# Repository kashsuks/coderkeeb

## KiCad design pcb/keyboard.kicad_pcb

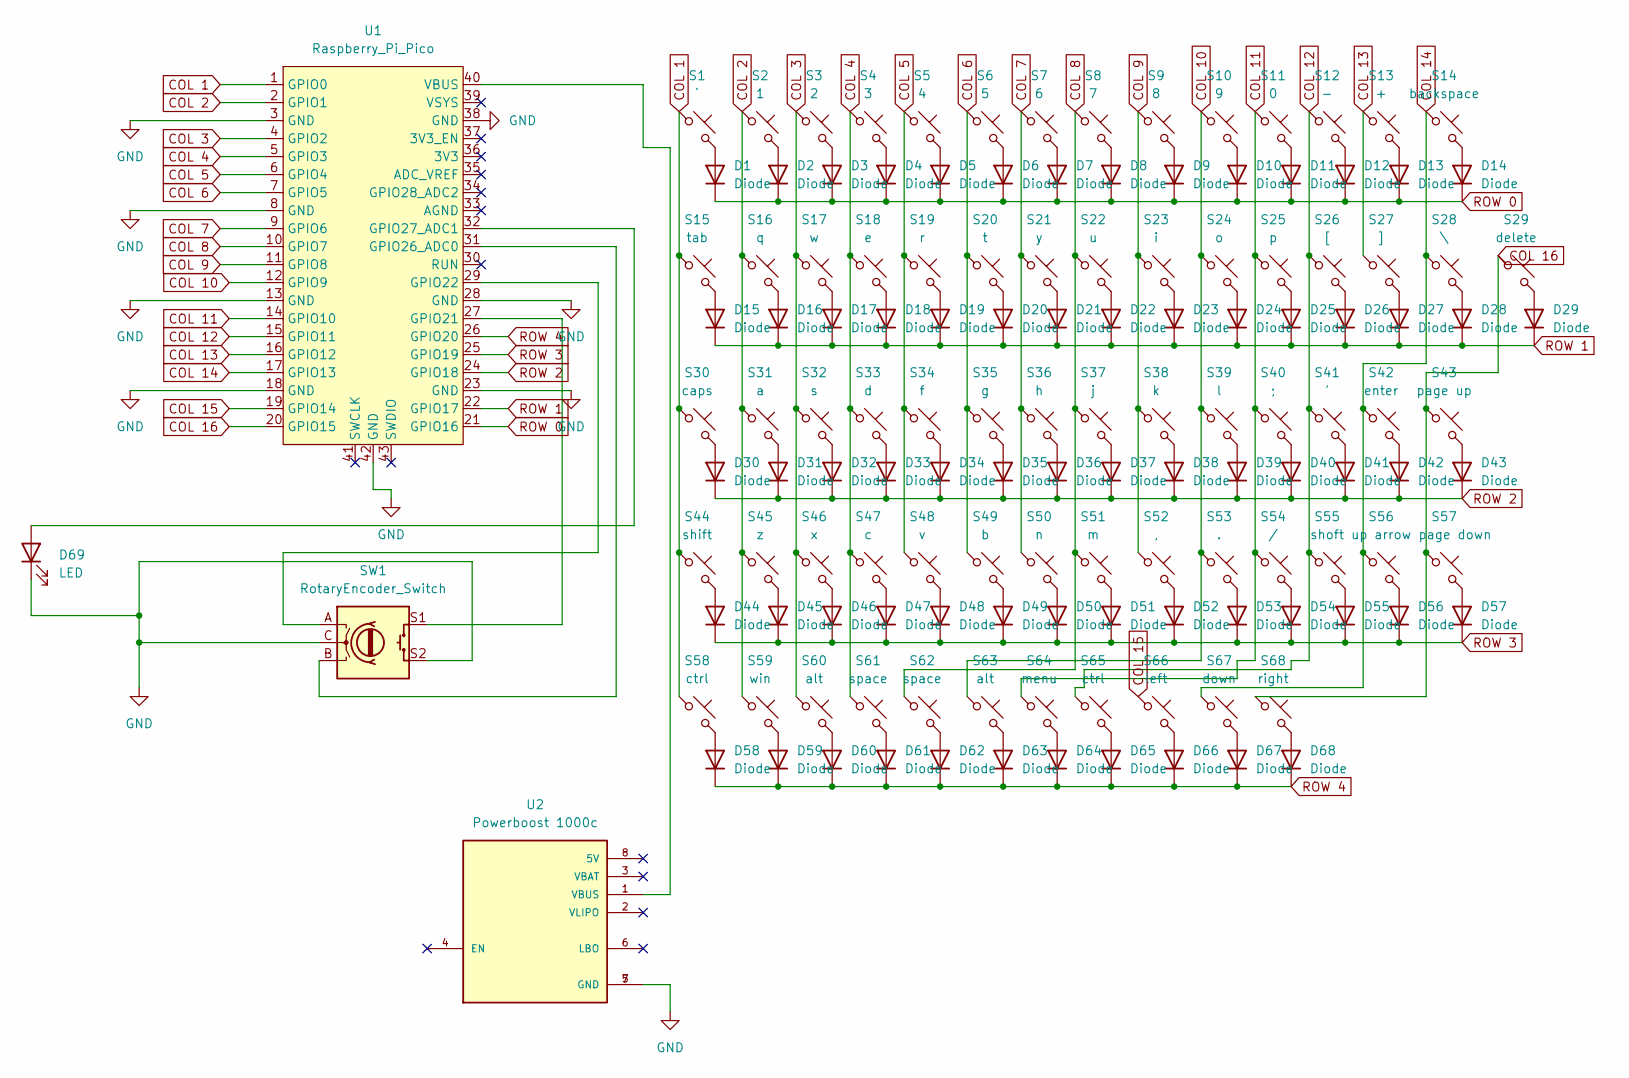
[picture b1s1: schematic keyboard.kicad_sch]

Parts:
D1, D2, D3, D4, D5, D6, D7, D8, D9, D10, D11, D12, D13, D14, D15, D16, D17, D18, D19, D20, D21, D22, D23, D24, D25, D26, D27, D28, D29, D30, D31, D32, D33, D34, D35, D36, D37, D38, D39, D40, D41, D42, D43, D44, D45, D46, D47, D48, D49, D50, D51, D52, D53, D54, D55, D56, D57, D58, D59, D60, D61, D62, D63, D64, D65, D66, D67, D68: Diode; Diode_DO-35
D69: LED; LED_D5.0mm
S1: `; Choc_V1
S2: 1; Choc_V1
S3: 2; Choc_V1
S4: 3; Choc_V1
S5: 4; Choc_V1
S6: 5; Choc_V1
S7: 6; Choc_V1
S8: 7; Choc_V1
S9: 8; Choc_V1
S10: 9; Choc_V1
S11: 0; Choc_V1
S12: -; Choc_V1
S13: +; Choc_V1
S14: backspace; Choc_V1
S15: tab; Choc_V1
S16: q; Choc_V1
S17: w; Choc_V1
S18: e; Choc_V1
S19: r; Choc_V1
S20: t; Choc_V1
S21: y; Choc_V1
S22: u; Choc_V1
S23: i; Choc_V1
S24: o; Choc_V1
S25: p; Choc_V1
S26: [; Choc_V1
S27: ]; Choc_V1
S28: \; Choc_V1
S29: delete; Choc_V1
S30: caps; Choc_V1
S31: a; Choc_V1
S32: s; Choc_V1
S33: d; Choc_V1
S34: f; Choc_V1
S35: g; Choc_V1
S36: h; Choc_V1
S37: j; Choc_V1
S38: k; Choc_V1
S39: l; Choc_V1
S40: ;; Choc_V1
S41: '; Choc_V1
S42: enter; Choc_V1
S43: page up; Choc_V1
S44: shift; Choc_V1
S45: z; Choc_V1
S46: x; Choc_V1
S47: c; Choc_V1
S48: v; Choc_V1
S49: b; Choc_V1
S50: n; Choc_V1
S51: m; Choc_V1
S52: ,; Choc_V1
S53: .; Choc_V1
S54: /; Choc_V1
S55: shoft; Choc_V1
S56: up arrow; Choc_V1
S57: page down; Choc_V1
S58, S65: ctrl; Choc_V1
S59: win; Choc_V1
S60, S63: alt; Choc_V1
S61, S62: space; Choc_V1
S64: menu; Choc_V1
S66: left; Choc_V1
S67: down; Choc_V1
S68: right; Choc_V1
SW1: RotaryEncoder_Switch; Encoder_EC11_MX
U1: Raspberry_Pi_Pico
U2: Powerboost 1000c; MODULE_2465; PARTREV B

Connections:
COL 1: S1.1, S15.1, S30.1, S44.1, S58.1, U1.1 (GPIO0)
COL 2: S2.1, S16.1, S31.1, S45.1, S59.1, U1.2 (GPIO1)
COL 3: S3.1, S17.1, S32.1, S46.1, S60.1, U1.4 (GPIO2)
COL 4: S4.1, S18.1, S33.1, S47.1, S61.1, U1.5 (GPIO3)
COL 5: S5.1, S19.1, S34.1, S48.1, U1.6 (GPIO4)
COL 6: S6.1, S20.1, S35.1, S49.1, U1.7 (GPIO5)
COL 7: S7.1, S21.1, S36.1, S50.1, U1.9 (GPIO6)
COL 8: S8.1, S22.1, S37.1, S51.1, S62.1, U1.10 (GPIO7)
COL 9: S9.1, S23.1, S38.1, S52.1, U1.11 (GPIO8)
COL 10: S10.1, S24.1, S39.1, S53.1, S63.1, U1.12 (GPIO9)
COL 11: S11.1, S25.1, S40.1, S54.1, S64.1, U1.14 (GPIO10)
COL 12: S12.1, S26.1, S41.1, S55.1, S65.1, U1.15 (GPIO11)
COL 13: S13.1, S27.1, U1.16 (GPIO12)
COL 14: S14.1, S28.1, S42.1, S56.1, S67.1, U1.17 (GPIO13)
COL 15: S66.1, U1.19 (GPIO14)
COL 16: S29.1, S43.1, S57.1, S68.1, U1.20 (GPIO15)
GND: D69.1 (K), SW1.C, SW1.S2, U1.3 (GND), U1.8 (GND), U1.13 (GND), U1.18 (GND), U1.23 (GND), U1.28 (GND), U1.38 (GND), U1.42 (GND), U2.5 (GND), U2.7 (GND)
unnamed: D1.2 (A), S1.2
unnamed: D2.2 (A), S2.2
unnamed: D3.2 (A), S3.2
unnamed: D4.2 (A), S4.2
unnamed: D5.2 (A), S5.2
unnamed: D6.2 (A), S6.2
unnamed: D7.2 (A), S7.2
unnamed: D8.2 (A), S8.2
unnamed: D9.2 (A), S9.2
unnamed: D10.2 (A), S10.2
unnamed: D11.2 (A), S11.2
unnamed: D12.2 (A), S12.2
unnamed: D13.2 (A), S13.2
unnamed: D14.2 (A), S14.2
unnamed: D15.2 (A), S15.2
unnamed: D16.2 (A), S16.2
unnamed: D17.2 (A), S17.2
unnamed: D18.2 (A), S18.2
unnamed: D19.2 (A), S19.2
unnamed: D20.2 (A), S20.2
unnamed: D21.2 (A), S21.2
unnamed: D22.2 (A), S22.2
unnamed: D23.2 (A), S23.2
unnamed: D24.2 (A), S24.2
unnamed: D25.2 (A), S25.2
unnamed: D26.2 (A), S26.2
unnamed: D27.2 (A), S27.2
unnamed: D28.2 (A), S28.2
unnamed: D29.2 (A), S29.2
unnamed: D30.2 (A), S30.2
unnamed: D31.2 (A), S31.2
unnamed: D32.2 (A), S32.2
unnamed: D33.2 (A), S33.2
unnamed: D34.2 (A), S34.2
unnamed: D35.2 (A), S35.2
unnamed: D36.2 (A), S36.2
unnamed: D37.2 (A), S37.2
unnamed: D38.2 (A), S38.2
unnamed: D39.2 (A), S39.2
unnamed: D40.2 (A), S40.2
unnamed: D41.2 (A), S41.2
unnamed: D42.2 (A), S42.2
unnamed: D43.2 (A), S43.2
unnamed: D44.2 (A), S44.2
unnamed: D45.2 (A), S45.2
unnamed: D46.2 (A), S46.2
unnamed: D47.2 (A), S47.2
unnamed: D48.2 (A), S48.2
unnamed: D49.2 (A), S49.2
unnamed: D50.2 (A), S50.2
unnamed: D51.2 (A), S51.2
unnamed: D52.2 (A), S52.2
unnamed: D53.2 (A), S53.2
unnamed: D54.2 (A), S54.2
unnamed: D55.2 (A), S55.2
unnamed: D56.2 (A), S56.2
unnamed: D57.2 (A), S57.2
unnamed: D58.2 (A), S58.2
unnamed: D59.2 (A), S59.2
unnamed: D60.2 (A), S60.2
unnamed: D61.2 (A), S61.2
unnamed: D62.2 (A), S62.2
unnamed: D63.2 (A), S63.2
unnamed: D64.2 (A), S64.2
unnamed: D65.2 (A), S65.2
unnamed: D66.2 (A), S66.2
unnamed: D67.2 (A), S67.2
unnamed: D68.2 (A), S68.2
unnamed: D69.2 (A), U1.32 (GPIO27_ADC1)
unnamed: SW1.S1, U1.27 (GPIO21)
unnamed: SW1.A, U1.29 (GPIO22)
unnamed: SW1.B, U1.31 (GPIO26_ADC0)
unnamed: U1.40 (VBUS), U2.1 (VBUS)
ROW 0: D1.1 (K), D2.1 (K), D3.1 (K), D4.1 (K), D5.1 (K), D6.1 (K), D7.1 (K), D8.1 (K), D9.1 (K), D10.1 (K), D11.1 (K), D12.1 (K), D13.1 (K), D14.1 (K), U1.21 (GPIO16)
ROW 1: D15.1 (K), D16.1 (K), D17.1 (K), D18.1 (K), D19.1 (K), D20.1 (K), D21.1 (K), D22.1 (K), D23.1 (K), D24.1 (K), D25.1 (K), D26.1 (K), D27.1 (K), D28.1 (K), D29.1 (K), U1.22 (GPIO17)
ROW 2: D30.1 (K), D31.1 (K), D32.1 (K), D33.1 (K), D34.1 (K), D35.1 (K), D36.1 (K), D37.1 (K), D38.1 (K), D39.1 (K), D40.1 (K), D41.1 (K), D42.1 (K), D43.1 (K), U1.24 (GPIO18)
ROW 3: D44.1 (K), D45.1 (K), D46.1 (K), D47.1 (K), D48.1 (K), D49.1 (K), D50.1 (K), D51.1 (K), D52.1 (K), D53.1 (K), D54.1 (K), D55.1 (K), D56.1 (K), D57.1 (K), U1.25 (GPIO19)
ROW 4: D58.1 (K), D59.1 (K), D60.1 (K), D61.1 (K), D62.1 (K), D63.1 (K), D64.1 (K), D65.1 (K), D66.1 (K), D67.1 (K), D68.1 (K), U1.26 (GPIO20)

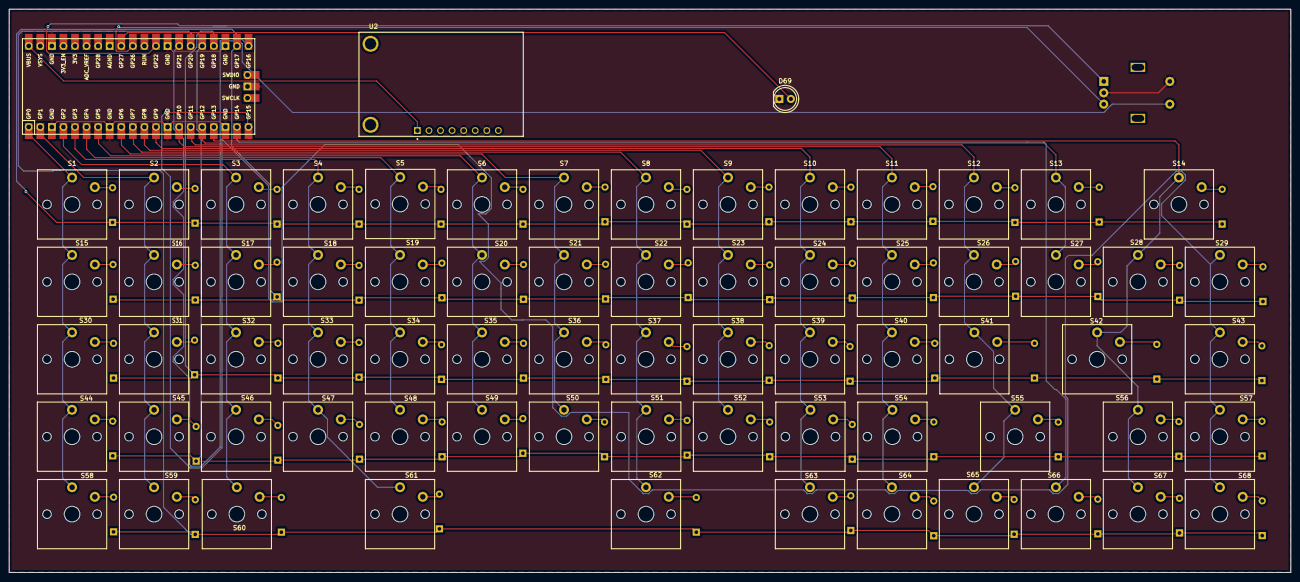
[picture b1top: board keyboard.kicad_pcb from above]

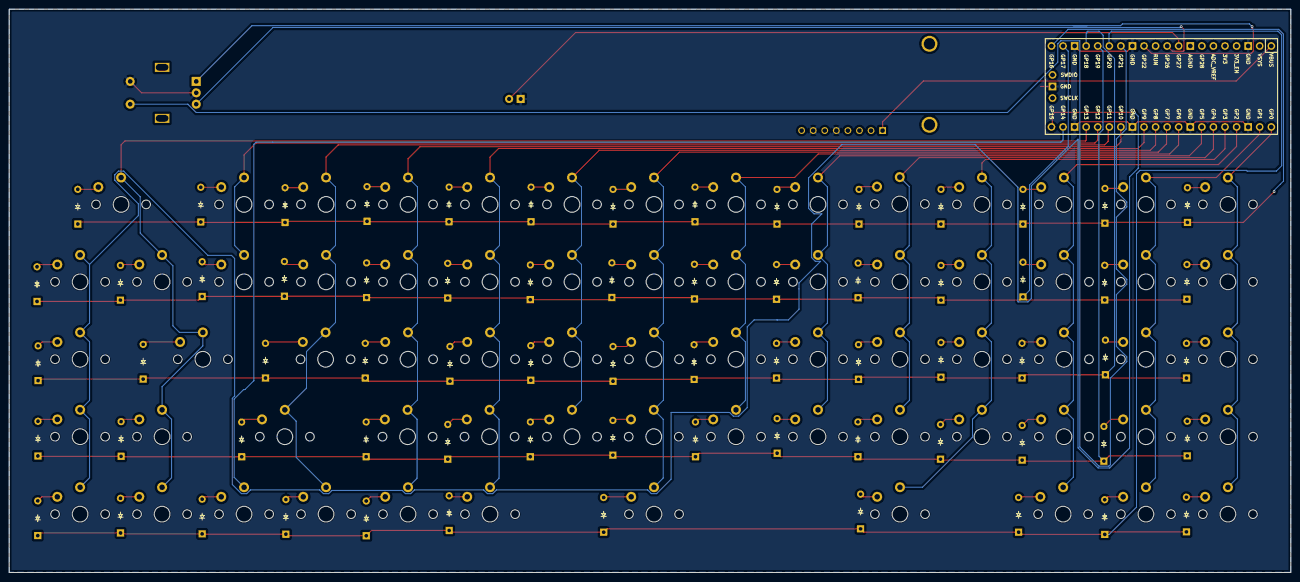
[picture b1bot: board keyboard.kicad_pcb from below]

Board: 2 copper layers, 281.4 x 123.7 mm, 140 parts (68 on the bottom side), 95 nets.

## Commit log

2025-06-06 Create something
2025-06-07 backups
